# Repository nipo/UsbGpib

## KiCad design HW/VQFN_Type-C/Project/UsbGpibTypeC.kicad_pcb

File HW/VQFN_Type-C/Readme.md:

# About

This is a redesign of the VQFN PCB with an USB Type-C connector.  It
also uses 0402 passives most of the time, LED and >= 1uF caps are 0603.

All components are laid out on Top layer, this allows to mount with
stenciling and hot plate.

In Release directory, `UsbGpibTypeC_A.zip`, `UsbGpibTypeC_A_BOM.csv`
and `UsbGpibTypeC_A-pos-JLC.xls` can be used directly with JLCPCB SMT
service.

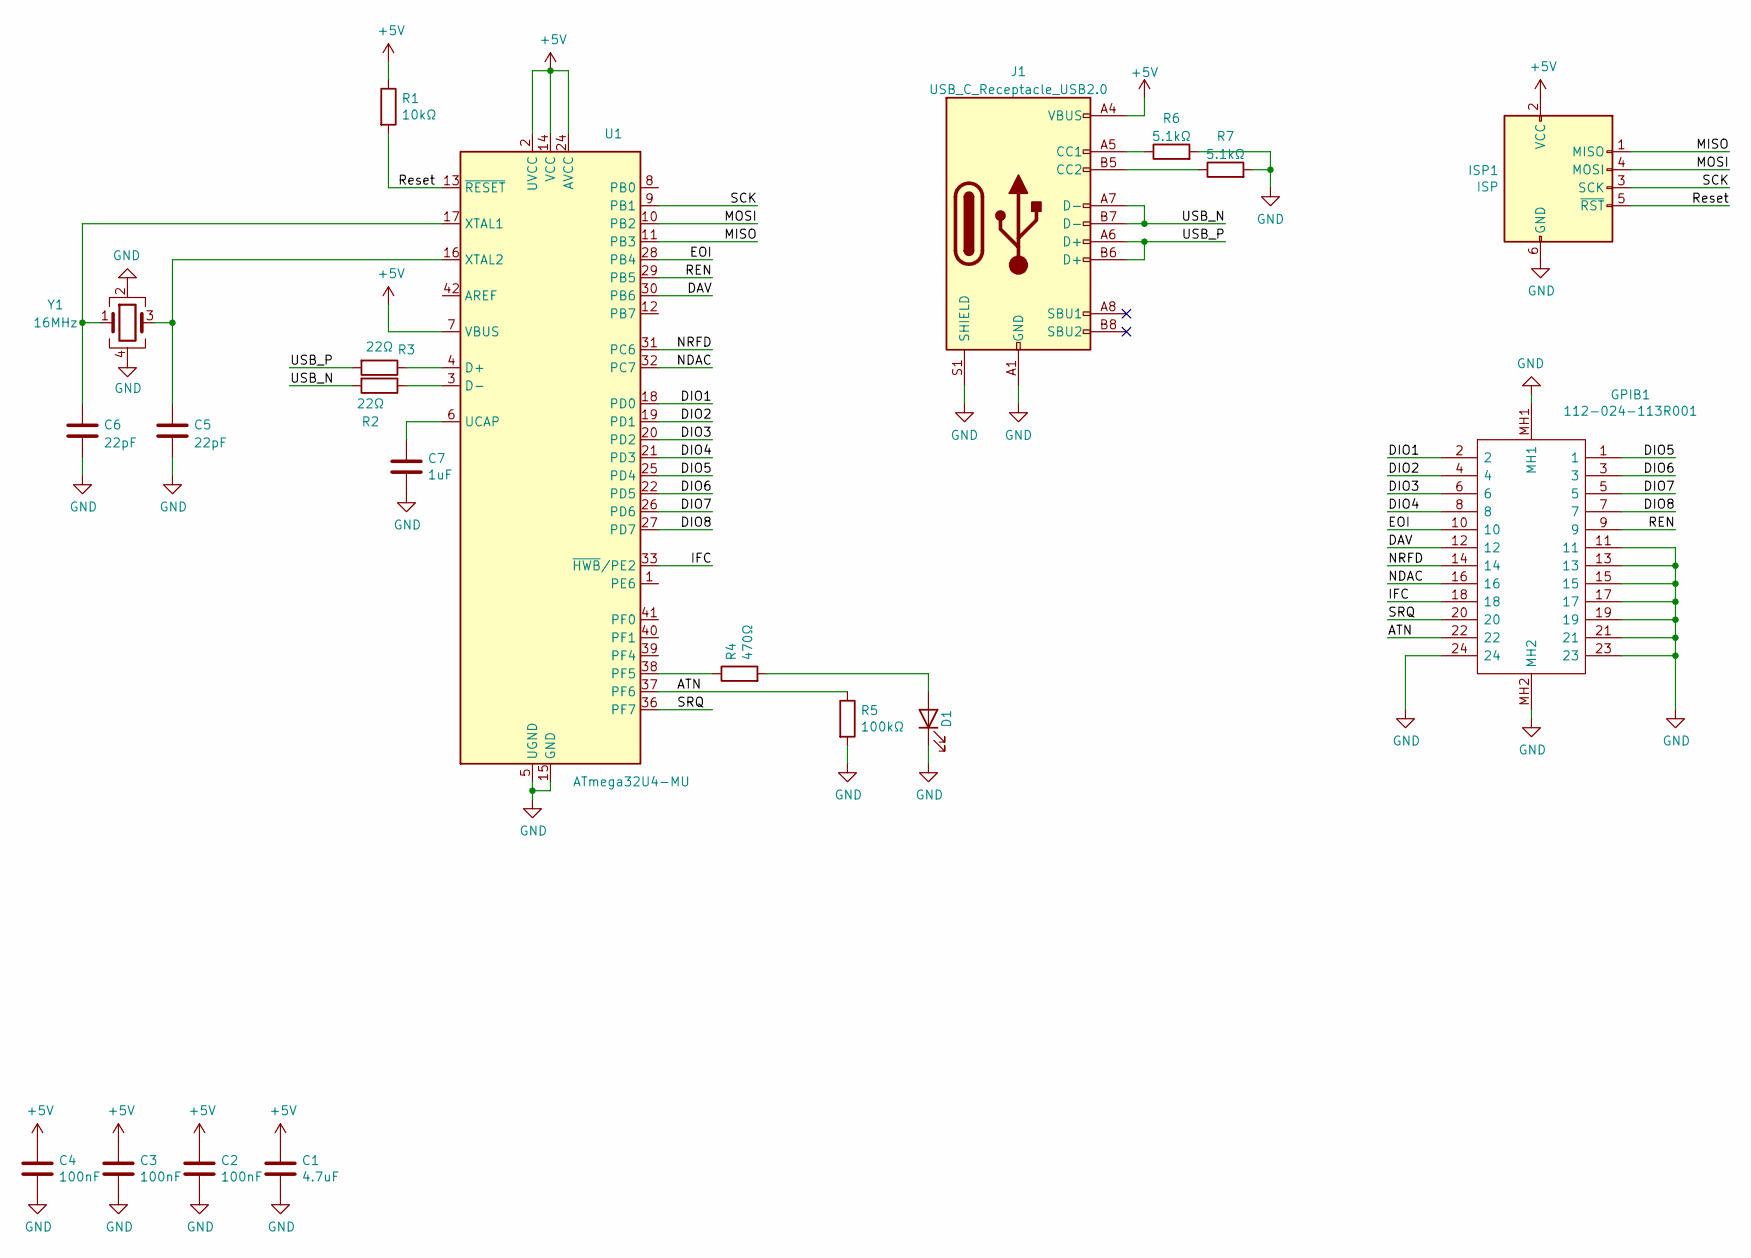
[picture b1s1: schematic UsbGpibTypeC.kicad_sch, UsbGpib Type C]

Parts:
C1: 4.7uF; C_0603_1608Metric; LCSC C19666
C2, C3, C4: 100nF; C_0402_1005Metric; LCSC C1525
C5, C6: 22pF; C_0402_1005Metric; LCSC C1555
C7: 1uF; C_0603_1608Metric; LCSC C15849
D1: Red; LED_0603_1608Metric; LCSC C965799
GPIB1: 112-024-113R001; 112024113R001; MPN 112-024-113R001; Digi-Key 1024RMA-ND
ISP1: ISP; PinHeader_2x03_P2.54mm_Vertical
J1: USB_C_Receptacle_USB2.0; CX90M-16P; MPN CX90M-16P; Digi-Key CX90M-16P
R1: 10kΩ; R_0402_1005Metric; LCSC C25744
R2, R3: 22Ω; R_0402_1005Metric; LCSC C25092
R4: 470Ω; R_0402_1005Metric; LCSC C25117
R5: 100kΩ; R_0402_1005Metric; LCSC C25741
R6, R7: 5.1kΩ; R_0402_1005Metric; LCSC C25905
U1: ATmega32U4-MU; QFN-44-1EP_7x7mm_P0.5mm_EP5.2x5.2mm; MPN ATMEGA32U4-MU; Digi-Key ATMEGA32U4-MU-ND
Y1: 16MHz; Crystal_SMD_3225-4Pin_3.2x2.5mm; LCSC C13738

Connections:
+5V: C1.1, C2.1, C3.1, C4.1, ISP1.2 (VCC), J1.A4 (VBUS), J1.A9 (VBUS), J1.B4 (VBUS), J1.B9 (VBUS), R1.1, U1.2 (UVCC), U1.7 (VBUS), U1.14 (VCC), U1.24 (AVCC), U1.34 (VCC), U1.44 (AVCC)
/ATN: GPIB1.22, R5.1, U1.37 (PF6)
/DAV: GPIB1.12, U1.30 (PB6)
/DIO1: GPIB1.2, U1.18 (PD0)
/DIO2: GPIB1.4, U1.19 (PD1)
/DIO3: GPIB1.6, U1.20 (PD2)
/DIO4: GPIB1.8, U1.21 (PD3)
/DIO5: GPIB1.1, U1.25 (PD4)
/DIO6: GPIB1.3, U1.22 (PD5)
/DIO7: GPIB1.5, U1.26 (PD6)
/DIO8: GPIB1.7, U1.27 (PD7)
/EOI: GPIB1.10, U1.28 (PB4)
/IFC: GPIB1.18, U1.33 (~HWB/PE2)
/MISO: ISP1.1 (MISO), U1.11 (PB3)
/MOSI: ISP1.4 (MOSI), U1.10 (PB2)
/NDAC: GPIB1.16, U1.32 (PC7)
/NRFD: GPIB1.14, U1.31 (PC6)
/REN: GPIB1.9, U1.29 (PB5)
/Reset: ISP1.5 (~RST), R1.2, U1.13 (~RESET)
/SCK: ISP1.3 (SCK), U1.9 (PB1)
/SRQ: GPIB1.20, U1.36 (PF7)
/USB_N: J1.A7 (D-), J1.B7 (D-), R2.2
/USB_P: J1.A6 (D+), J1.B6 (D+), R3.2
GND: C1.2, C2.2, C3.2, C4.2, C5.2, C6.2, C7.2, D1.1 (K), GPIB1.11, GPIB1.13, GPIB1.15, GPIB1.17, GPIB1.19, GPIB1.21, GPIB1.23, GPIB1.24, GPIB1.MH1, GPIB1.MH2, ISP1.6 (GND), J1.A1 (GND), J1.A12 (GND), J1.B1 (GND), J1.B12 (GND), J1.S1 (SHIELD), R5.2, R6.2, R7.2, U1.5 (UGND), U1.15 (GND), U1.23 (GND), U1.35 (GND), U1.43 (GND), U1.45 (GND), Y1.2, Y1.4
unnamed: C5.1, U1.16 (XTAL2), Y1.3
unnamed: C6.1, U1.17 (XTAL1), Y1.1
unnamed: C7.1, U1.6 (UCAP)
unnamed: D1.2 (A), R4.2
unnamed: J1.A5 (CC1), R6.1
unnamed: J1.B5 (CC2), R7.1
unnamed: R2.1, U1.3 (D-)
unnamed: R3.1, U1.4 (D+)
unnamed: R4.1, U1.38 (PF5)

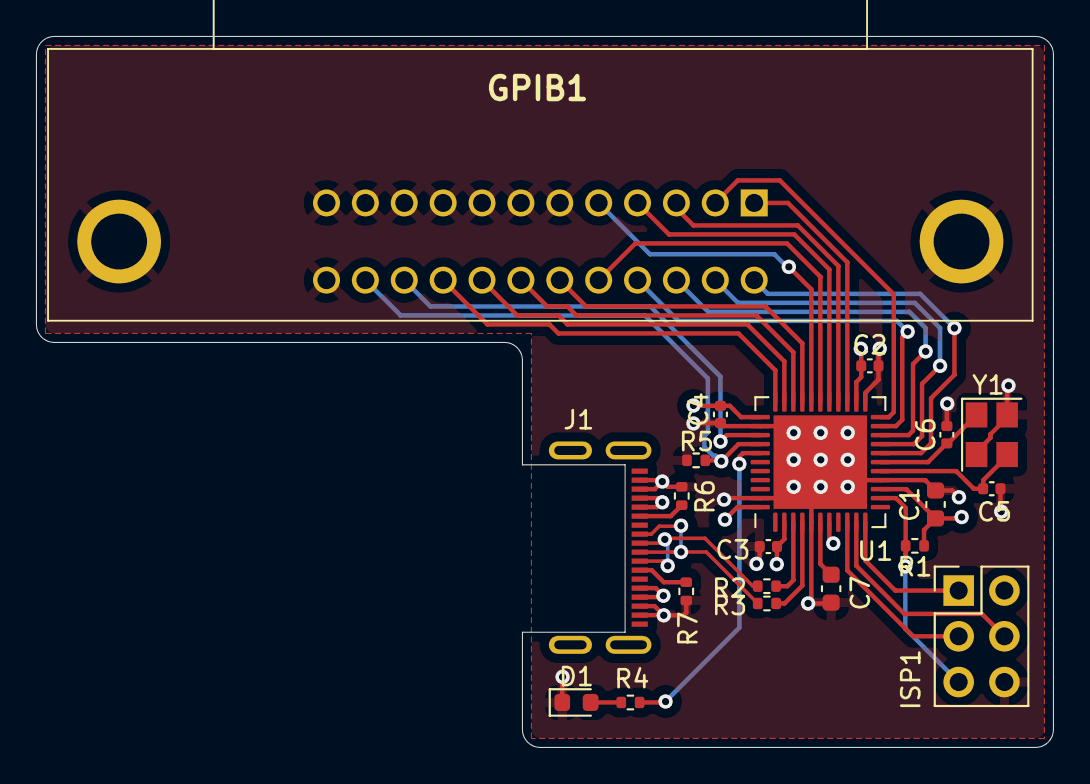
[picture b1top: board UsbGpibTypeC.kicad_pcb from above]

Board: 4 copper layers, 56.5 x 39.5 mm, 20 parts (0 on the bottom side), 33 nets.

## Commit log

2023-01-10 SW/TestAndMeasurement: Scan addresses from high values first
    The scan is taking the first address that responds, but then looks
    for lower matching address (masked with 0x1f) if >= 0x20. If we scan
    from low addresses first, we can never get to this case.
2023-01-10 HW: Move versions around
2023-01-11 HW: Add Type-C version
2023-01-11 Add ignores
2023-01-11 SW/TestAndMeasurement: Encapsulate internal settings
2023-01-11 HW: Remove local settings
2023-01-11 SW/TestAndMeasurement: Add vendor requests to get/set settings
2023-01-11 Update binaries
2023-01-11 SW/TestAndMeasurement: Fix control request parsing
    Setup packet's bmRequestType Type and Recipient fields are enumerated,
    they were trated as bitfields.
2023-01-11 SW/TestAndMeasurement: Also try legacy 'ID' command for SN gathering
    This is used by pre-GPIB devices like HP5385A (HP-IB).
2023-01-11 SW/TestAndMeasurement: Silent warning about int as pointer
2023-01-11 Tools: Add management tool
2023-01-28 Add mounted board images
